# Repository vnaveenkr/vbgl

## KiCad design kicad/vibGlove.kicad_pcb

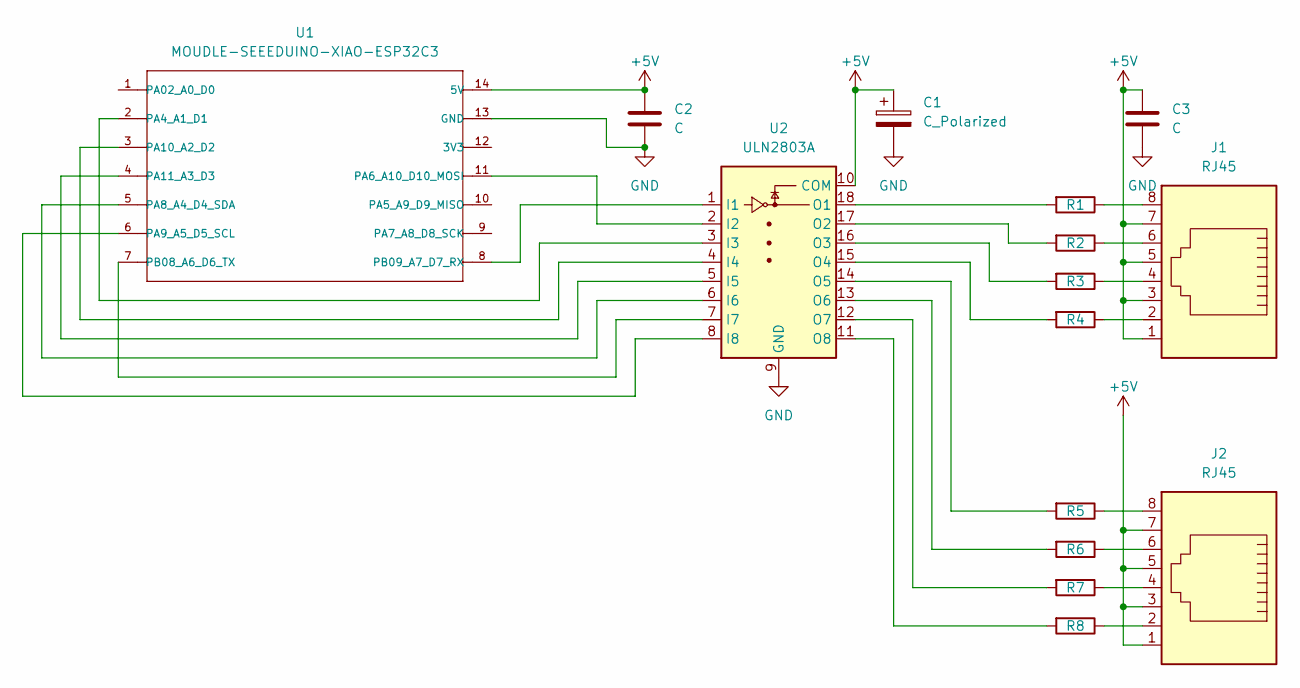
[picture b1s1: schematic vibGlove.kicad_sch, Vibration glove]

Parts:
C1: C_Polarized; CP_Radial_D5.0mm_P2.50mm
C2, C3: C; C_Disc_D3.0mm_W1.6mm_P2.50mm
J1, J2: RJ45; TE_RJ45-8N3-B
R1, R2, R3, R4, R5, R6, R7, R8: R; R_Axial_DIN0204_L3.6mm_D1.6mm_P7.62mm_Horizontal
U1: MOUDLE-SEEEDUINO-XIAO-ESP32C3; MOUDLE14P-SMD-2.54-21X17.8MM
U2: ULN2803A; DIP-18_STM

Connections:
+5V: C1.1, C2.1, C3.1, J1.1, J1.3, J1.5, J1.7, J2.1, J2.3, J2.5, J2.7, U1.14 (5V), U2.10 (COM)
GND: C1.2, C2.2, C3.2, U1.13 (GND), U2.9 (GND)
unnamed: J1.2, R4.1
unnamed: J1.4, R3.1
unnamed: J1.6, R2.1
unnamed: J1.8, R1.1
unnamed: J2.2, R8.1
unnamed: J2.4, R7.1
unnamed: J2.6, R6.1
unnamed: J2.8, R5.1
unnamed: U1.2 (PA4_A1_D1), U2.3 (I3)
unnamed: U1.11 (PA6_A10_D10_MOSI), U2.2 (I2)
unnamed: U1.5 (PA8_A4_D4_SDA), U2.6 (I6)
unnamed: U1.6 (PA9_A5_D5_SCL), U2.8 (I8)
unnamed: U1.3 (PA10_A2_D2), U2.4 (I4)
unnamed: U1.4 (PA11_A3_D3), U2.5 (I5)
unnamed: U1.7 (PB08_A6_D6_TX), U2.7 (I7)
unnamed: U1.8 (PB09_A7_D7_RX), U2.1 (I1)
unnamed: R1.2, U2.18 (O1)
unnamed: R2.2, U2.17 (O2)
unnamed: R3.2, U2.16 (O3)
unnamed: R4.2, U2.15 (O4)
unnamed: R5.2, U2.14 (O5)
unnamed: R6.2, U2.13 (O6)
unnamed: R7.2, U2.12 (O7)
unnamed: R8.2, U2.11 (O8)

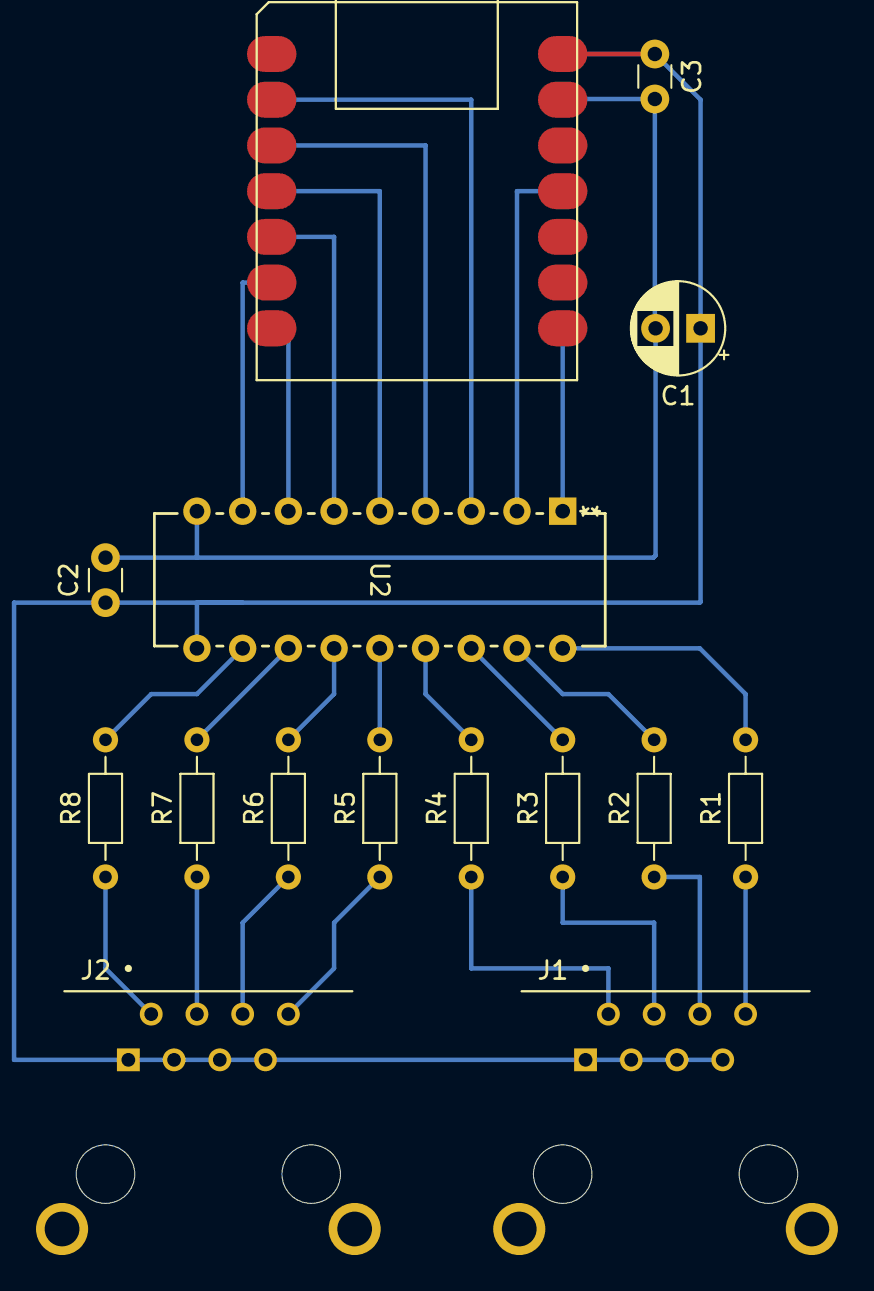
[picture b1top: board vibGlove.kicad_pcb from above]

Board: 2 copper layers, 15 parts (0 on the bottom side), 26 nets.

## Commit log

2024-03-29 the beginning
2024-03-29 minor
2024-03-29 Add service worker
2024-03-29 Change sw scope
2024-03-30 center align, ++ font size
2024-04-05 remove service worker
2024-04-09 Add XIAO esp32c3 firmware
2024-04-10 add cad files
2024-04-24 prevent apply button being disabled.
